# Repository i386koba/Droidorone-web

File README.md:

# Droidorone-web
* Droidorone は セルコンと改名し、セルコン プロジェクト全体は https://github.com/cellucon/ です。

* https://i386koba.github.io/Droidorone-web/ で旧画面を開けます。
* 航路の記録は https://i386koba.github.io/Droidorone-web/mapLink.html から参照できます。

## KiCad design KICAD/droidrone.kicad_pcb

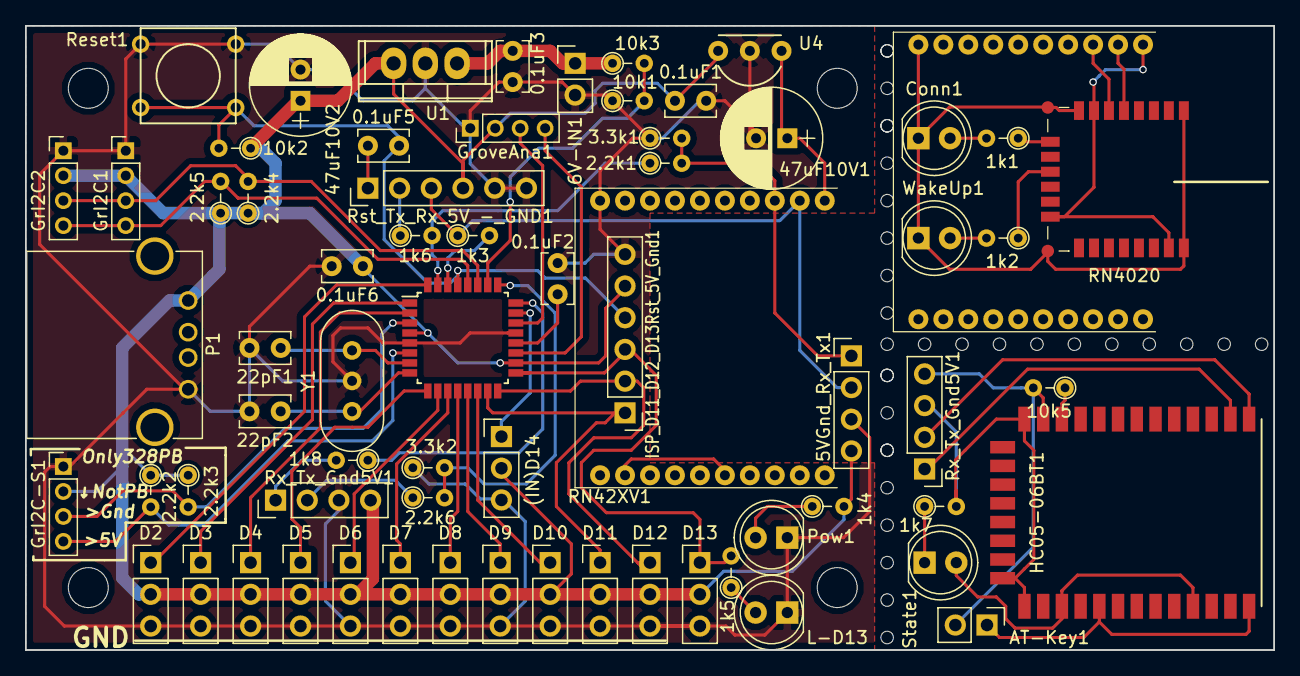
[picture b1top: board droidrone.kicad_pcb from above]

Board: 2 copper layers, 100.0 x 50.0 mm, 68 parts (0 on the bottom side), 57 nets.

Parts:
0.1uF1, 0.1uF2, 0.1uF3, 0.1uF5, 0.1uF6: 0.1uF; C_Rect_L4.0mm_W2.5mm_P2.50mm
1k1, 1k2, 1k3, 1k4, 1k5, 1k6, 1k7, 1k8: 1k; R_Axial_DIN0204_L3.6mm_D1.6mm_P2.54mm_Vertical
2.2k1, 2.2k2, 2.2k3, 2.2k4, 2.2k5, 2.2k6: 2.2k; R_Axial_DIN0204_L3.6mm_D1.6mm_P2.54mm_Vertical
3.3k1, 3.3k2: 3.3k; R_Axial_DIN0204_L3.6mm_D1.6mm_P2.54mm_Vertical
5VGnd_Rx_Tx1: CONN_01X04; Pin_Header_Straight_1x04_Pitch2.54mm
6V-IN1: CONN_01X02; Pin_Header_Straight_1x02_Pitch2.54mm
10k1, 10k2, 10k3, 10k5: 10k; R_Axial_DIN0204_L3.6mm_D1.6mm_P2.54mm_Vertical
22pF1, 22pF2: 22pF; C_Rect_L4.0mm_W2.5mm_P2.50mm
47uF10V1, 47uF10V2: 47uF 10V; CP_Radial_D8.0mm_P2.50mm
(IN)D14: CONN_01X03; Pin_Header_Straight_1x03_Pitch2.54mm
AT-Key1: JUMPER; Pin_Header_Straight_1x02_Pitch2.54mm
Conn1: LED; LED_D5.0mm
D2, D3, D4, D5, D6, D7, D8, D9, D10, D11, D12, D13: CONN_01X03; Pin_Header_Straight_1x03_Pitch2.54mm
GrI2C1, GrI2C2, GrI2C-S1: CONN_01X04; Pin_Header_Straight_1x04_Pitch2.00mm
GroveAna1: CONN_01X04; Pin_Header_Straight_1x04_Pitch2.00mm
HC05-06BT1: ITEAD_HC-05; HC-05-06
IC1: ATMEGA328PB; LQFP-32_7x7mm_Pitch0.8mm
ISP_D11_D12_D13Rst_5V_Gnd1: CONN_01X06; Pin_Header_Straight_1x06_Pitch2.54mm
L-D13: LED; LED_D5.0mm
P1: USB_A
Pow1: LED; LED_D5.0mm
RN42XV1, RN42XV2: RN42XV
RN4020: RN4020; RN2040
Reset1: SW_PUSH; SW_PUSH_SMALL
Rst_Tx_Rx_5V_-_GND1: CONN_01X06; Pin_Header_Straight_1x06_Pitch2.54mm
Rx_Tx_Gnd5V1, Rx_Tx_Gnd5V1#2: CONN_01X04; Pin_Header_Straight_1x04_Pitch2.54mm
State1: LED; LED_D5.0mm
U1: LM7805CT; TO-220
U4: LP2950L-3.3V; LP2950
WakeUp1: LED; LED_D5.0mm
Y1: Crystal; Crystal_HC49-U-3pin_Vertical

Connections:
+3V3: 47uF10V1.1, RN42XV1.1, U4.1
+5V: 0.1uF1.1, 0.1uF6.1, 1k4.2, 2.2k2.1, 2.2k3.1, 2.2k4.1, 2.2k5.1, 5VGnd_Rx_Tx1.4, 10k2.1, 47uF10V2.1, (IN)D14.2, D2.2, D3.2, D4.2, D5.2, D6.2, D7.2, D8.2, D9.2, D10.2, D11.2, D12.2, D13.2, GrI2C1.2, GrI2C2.2, GrI2C-S1.2, GroveAna1.2, IC1.4, IC1.18, ISP_D11_D12_D13Rst_5V_Gnd1.5, P1.1, Rst_Tx_Rx_5V_-_GND1.4, Rx_Tx_Gnd5V1#2.4, U1.3, U4.3
+6V: 0.1uF3.1, 6V-IN1.1, 10k3.1, U1.1
/D2: D2.1, IC1.32
/D3(P): D3.1, IC1.1
/D4: D4.1, IC1.2
/D5(P): D5.1, IC1.9
/D6(P): D6.1, IC1.10
/D7: D7.1, IC1.11
/D8: D8.1, IC1.12
/D9: D9.1, IC1.13
/D10: D10.1, IC1.14
/D11(P): D11.1, IC1.15, ISP_D11_D12_D13Rst_5V_Gnd1.1
/D12: D12.1, IC1.16, ISP_D11_D12_D13Rst_5V_Gnd1.2
/D13: 1k5.2, D13.1, IC1.17, ISP_D11_D12_D13Rst_5V_Gnd1.3
/D14/A0: (IN)D14.1, IC1.23
/D15/A1: 1k8.1, IC1.24
/D16/A2: 2.2k6.2, 3.3k2.2, IC1.25
/D17/A3: 10k1.2, 10k3.2, IC1.26
/D18/A4/SDA: 2.2k4.2, GrI2C1.3, GrI2C2.3, IC1.27
/D19/A5/SCL: 2.2k5.2, GrI2C1.4, GrI2C2.4, IC1.28
/RXD: 1k3.2, IC1.30
/TXD: 1k6.2, 2.2k1.1, IC1.31
GND: 0.1uF1.2, 0.1uF2.1, 0.1uF3.2, 0.1uF6.2, 3.3k1.1, 3.3k2.1, 5VGnd_Rx_Tx1.3, 6V-IN1.2, 10k1.1, 22pF1.2, 22pF2.2, 47uF10V1.2, 47uF10V2.2, (IN)D14.3, D2.3, D3.3, D4.3, D5.3, D6.3, D7.3, D8.3, D9.3, D10.3, D11.3, D12.3, D13.3, GrI2C1.1, GrI2C2.1, GrI2C-S1.1, GroveAna1.1, IC1.5, IC1.21, ISP_D11_D12_D13Rst_5V_Gnd1.6, L-D13.1, P1.4, Pow1.1, RN42XV1.10, Reset1.1, Rst_Tx_Rx_5V_-_GND1.5, Rst_Tx_Rx_5V_-_GND1.6, Rx_Tx_Gnd5V1#2.3, U1.2, U4.2, Y1.3
unnamed: 0.1uF2.2, IC1.20
unnamed: 0.1uF5.1, Rst_Tx_Rx_5V_-_GND1.1
unnamed: 0.1uF5.2, 10k2.2, IC1.29, ISP_D11_D12_D13Rst_5V_Gnd1.4, Reset1.2
unnamed: 1k1.1, RN4020.10
unnamed: 1k1.2, Conn1.2
unnamed: 1k2.1, RN4020.12
unnamed: 1k2.2, WakeUp1.2
unnamed: 1k3.1, 5VGnd_Rx_Tx1.2, RN42XV1.2, Rst_Tx_Rx_5V_-_GND1.3
unnamed: 1k4.1, Pow1.2
unnamed: 1k5.1, L-D13.2
unnamed: 1k6.1, Rst_Tx_Rx_5V_-_GND1.2
unnamed: 1k7.1, State1.1
unnamed: 1k7.2, HC05-06BT1.13, HC05-06BT1.21, HC05-06BT1.22, Rx_Tx_Gnd5V1.3
unnamed: 1k8.2, Rx_Tx_Gnd5V1#2.1
unnamed: 2.2k1.2, 3.3k1.2, 5VGnd_Rx_Tx1.1, RN42XV1.3
unnamed: 2.2k2.2, GrI2C-S1.4, IC1.6
unnamed: 2.2k3.2, GrI2C-S1.3, IC1.3
unnamed: 2.2k6.1, Rx_Tx_Gnd5V1#2.2
unnamed: 10k5.1, HC05-06BT1.11
unnamed: 10k5.2, AT-Key1.2, HC05-06BT1.12, Rx_Tx_Gnd5V1.4
unnamed: 22pF1.1, IC1.7, Y1.2
unnamed: 22pF2.1, IC1.8, Y1.1
unnamed: AT-Key1.1, HC05-06BT1.26, HC05-06BT1.34
unnamed: Conn1.1, RN42XV2.10, RN4020.1, RN4020.8, RN4020.9, RN4020.16, RN4020.24, WakeUp1.1
unnamed: GroveAna1.3, IC1.22
unnamed: GroveAna1.4, IC1.19
unnamed: HC05-06BT1.1, Rx_Tx_Gnd5V1.2
unnamed: HC05-06BT1.2, Rx_Tx_Gnd5V1.1
unnamed: HC05-06BT1.24, HC05-06BT1.31, State1.2
unnamed: RN42XV1.12, RN42XV1.16
unnamed: RN42XV2.2, RN4020.5
unnamed: RN42XV2.3, RN4020.6
unnamed: RN42XV2.1, RN4020.7, RN4020.15, RN4020.23

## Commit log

2016-10-24 Broadcast test1
2016-11-01 video strame url.
2016-11-02 マルチキャストテスト
2016-11-07 キャプチャーテスト
2016-11-08 video.videoWidth
2016-11-08 add snap shot.
2016-11-09 Video 自動回転１
2016-11-09 snap shot rotate.
2016-11-11 GoogleDriveフォルダ作成準備
2016-11-11 GD Make dir.
2016-11-11 mkdir.
2016-11-13 GD jpeg upload test.
2016-11-14 GoogleDrive jpeg upload 成功。
2016-11-14 コメント追加
2016-11-14 canvas test.
2016-11-14 GD jpeg upload test2.
2016-11-15 Android画面縦固定、GDアップロード画像にGPSデータ付随
2016-11-16 single peer obj.
2016-11-16 single peer obj.2
2016-11-17 maplink test.
2016-11-17 全ユーザートラック表示のテスト
2016-11-18 maplink test2.
2016-11-20 GD jpeg watch is ok.
2016-11-21 html add.
2016-11-22 lte level add. pid test1.
2016-11-25 pid test2
2016-11-30 add arduino ino file
2016-11-30 pid test2.
2016-12-02 pid制御実機、BTコマンド区別
2016-12-02 pid制御実機Test2
2016-12-05 正転、反転
2016-12-05 カメラ切り替え連続Fix
2016-12-06 pid 実機テスト2
2016-12-08 map link fix1
2016-12-08 map maker test.
2016-12-09 map link fix2 addlisner test.
2016-12-09 map maker test2.
2016-12-13 map maker test3.
2016-12-13 googleMap レイヤー表示
2017-01-05 gamepad 追加
2017-01-05 gamepad test2
2017-01-06 gamepad test3(OK) WindowのGamePad接続イベントが調子悪く、手動にした。
2017-01-10 PS2コントローラUSB変換で、Xinput変換ソフトx360ceでOK。
2017-01-12 GPS軌跡追加、導き対応GPSのAndroid入手のため。
2017-01-17 GPS軌跡追加、導き対応GPSのAndroid入手のため。FIX2
2017-01-17 gps test2
2017-01-18 GPS,ホイル回転選択 FIX1
2017-01-18 test 2.
2017-01-18 test3
2017-01-19 ブラウザ位置情報追加
2017-01-19 navigator.geolocation test1
2017-01-23 docs folder test http://qiita.com/tonkotsuboy_com/items/f98667b89228b98bc096
2017-01-25 KICAD 追加
2017-01-25 kicad add usb
2017-01-25 add lib
2017-01-26 kicad chg1.
2017-02-08 foot print update
2017-02-09 size 100x50
2017-02-09 add sub pcb
2017-02-10 same chg.
2017-02-13 chg sch
2017-02-13 add HC-06 BT mod
2017-02-14 配線開始
2017-02-14 配線終了
2017-02-17 配線終了2
2017-02-17 add comment.
2017-03-03 add firstframe.jpg
2017-03-03 same fix.
2017-03-09 グローバル編集調査
2017-03-09 グローバル編集調査2
2017-03-10 グローバル編集,GPS,エンコーダ軌跡分離
2017-03-13 GPS path chg.
2017-03-15 G-Drive保存条件についてテスト
2017-03-15 位置修正時のENCマーカー、パスを削除
2017-03-15 エンコーダ距離によってマップパス軌跡を追加
2017-03-16 終了時距離短ければG-Driveファイル削除OK。
2017-03-16 距離の短いものはGDドライブから削除（の予定がリロード時の処理がうまくいかない）
2017-10-19 chg title
2017-10-26 Create LICENSE
